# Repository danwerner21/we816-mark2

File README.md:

# WE816-MARK2
The WE816-MARK2 is the second iteration of a 16-bit 65816 based system with 512K of System RAM, 96K of System ROM, a Raspberry PI Pico based graphics processor and an AY-3-8910 Sound chip.  The system runs a custom version of BASIC and supports commodore compatible IEC disk drives.

EhBASIC by Lee Davison was ported to the 65816 CPU on the WE816 computer.   It is designed to allow a full 64K bank for BASIC code and variables with the BASIC interpreter running in a totally different bank. Full documentation on the basic intrepreter can be found in the support folder

---

## Bugs:
* V0.08 board
        U13 should be a 22V10 rather than a 20V8  (no patches required)
        U31 should be 74ALS245 rather than 74AC245 (no patches required)
        The Footprints for the expansion(J7) and Keyboard(J3) connectors are wrong -- special cables are required to connect this version to keyboard and expansion
        RTC IS STILL BROKEN, DO NOT POPULATE U7,U8,X3,C36,C37,C34,R1,R2,R3,U9,BT1,K4,JP1, & JP2

* V0.9 board
        U16 should not be populated -- the wait state generator is not functional, maximum successful tested clock speed is 2.4576 Mhz
        Higher CPU speeds are possible, but the video will not function at much beyond this speed.

## To Do:
* Document Jumper Settings
* Document IO Ports
* Memory Map
* Video speed is not fast enough to deal with a clock speed > (around) 2mhz (2.4576 works perfectly)  Need to add wait state hardware for video
* Add Pictures to this Document
---

## What is included in this repo?
As of this time, the repo includes

1. The WE816-Mark2 Mainboard PCB Kicad design and Gerber files
2. The source code and binaries for the WE816 BASIC interpreter
3. The source code and binaries for the WE816 BIOS firmware
4. The source code and binaries for several hardware test programs
5. The logic equasions for the 4 GALs
6. **OpenSCAD and STL files for a 3d printed case
7. The Firmware for the Raspberry Pi Pico Video  

---

## Known Bugs

### System Jumpers

Jumper P9 -- stereo channel mixer

 *  no jumpers, channel a left, channel c right, channel b left and right
 *  1-2 and 2-3 , channel a,b,c mixed to left and right

Jumper K1 - SRAM chip selection

 * 1&2 - 512K chip used (AS6C4008)
 * 2&3 - 128K chip used (AS6C1008)

Jumper K2 - ROM chip selection

 * 1&2 - 27c256 chip used
 * 2&3 - 29c256 chip used

Jumper K3 - ROM size

 * 1&2 - 16K rom page 0 memory map @ $C000
 * 2&3 - 32K rom page 0 memory map @ $8000

Power P1

 * 1- NC
 * 2-GND
 * 3-GND
 * 4-+5VDC 2A Regulated

Reset P2

 * NO Switch (Short to put system in reset)

Jumper J1, Interrupt Select

* 1&8 UART Interrupt enabled
* 2&7 VIA 1 Interrupt enabled
* 3&6 VIA 2 Interrupt enabled
* 4&5 TMS9918 Interrupt enabled

---

## Video Programming
IO PORTS

Address|Description|Value|Value
--------|--------|----------|--------
$fe30 | Scan Line Emulation | on | off
$fe31 | Display Page | page 0 | page 1
$fe32 | character generator write offset | write offset |
$fe33 | character generator write | Value |
$fe34 | device command  | Command |
$fe35 | Text Mode  | on | off
$fe36 | Lores Mode  | on | off
$fe37 | Double Lores Mode (must be in lores first)  | on | off
$fe38 | Hires Mode | on | off
$fe39 | Double Hires Mode (must be in hires first)  | on | off
$fe3A | 80 Col Mode (must be in text mode)  | on | off
$fe3b | Mixed Mode   (must be in lores/hires first) | on | off
$fe3c | Quad Hires  (must be in hires first) | on | off
$fe3d | Mono Hires  (must be in hires first)| on | off

## Bill Of Materials

### Mainboard

Qty|Reference(s)|Value
--------|--------|----------

### Keyboard
The Keyboard used in the WE816 is identical to the keyboard used in Sergey Kiselev's MSX compatible OMEGA computer.  See the Schematics, PCB layout and build instructions
[here](https://github.com/skiselev/omega/blob/master/Keyboard.md)

### Case
The case in the following images is a 3D print manufactured by the 3D print service offered by JLCPCB.com.  The case was originally designed to be 3D printed by a FDM printer such as the Anycubic Chiron.   It was originally intended that threaded inserts be melted into the stand off posts so the diameter of the holes were sized accordingly.  If a printing service (such as JLCPCB) is used that uses resin printing, it is necessary to slightly drill out the holes in the stand offs so that threaded inserts can be glued in.   It should also be noted that the design tolerances are quite tight and variations in printing can mean that some slight adjusting may be needed in order to get a good fit.

A 12V to 5V converter can be seen in the image that was added into the case in order to convert the 12V power input to the 5B required by the main board.

### Questions?

If there are any questions, I can be reached at vic2020Dan at gmail dot com.

---

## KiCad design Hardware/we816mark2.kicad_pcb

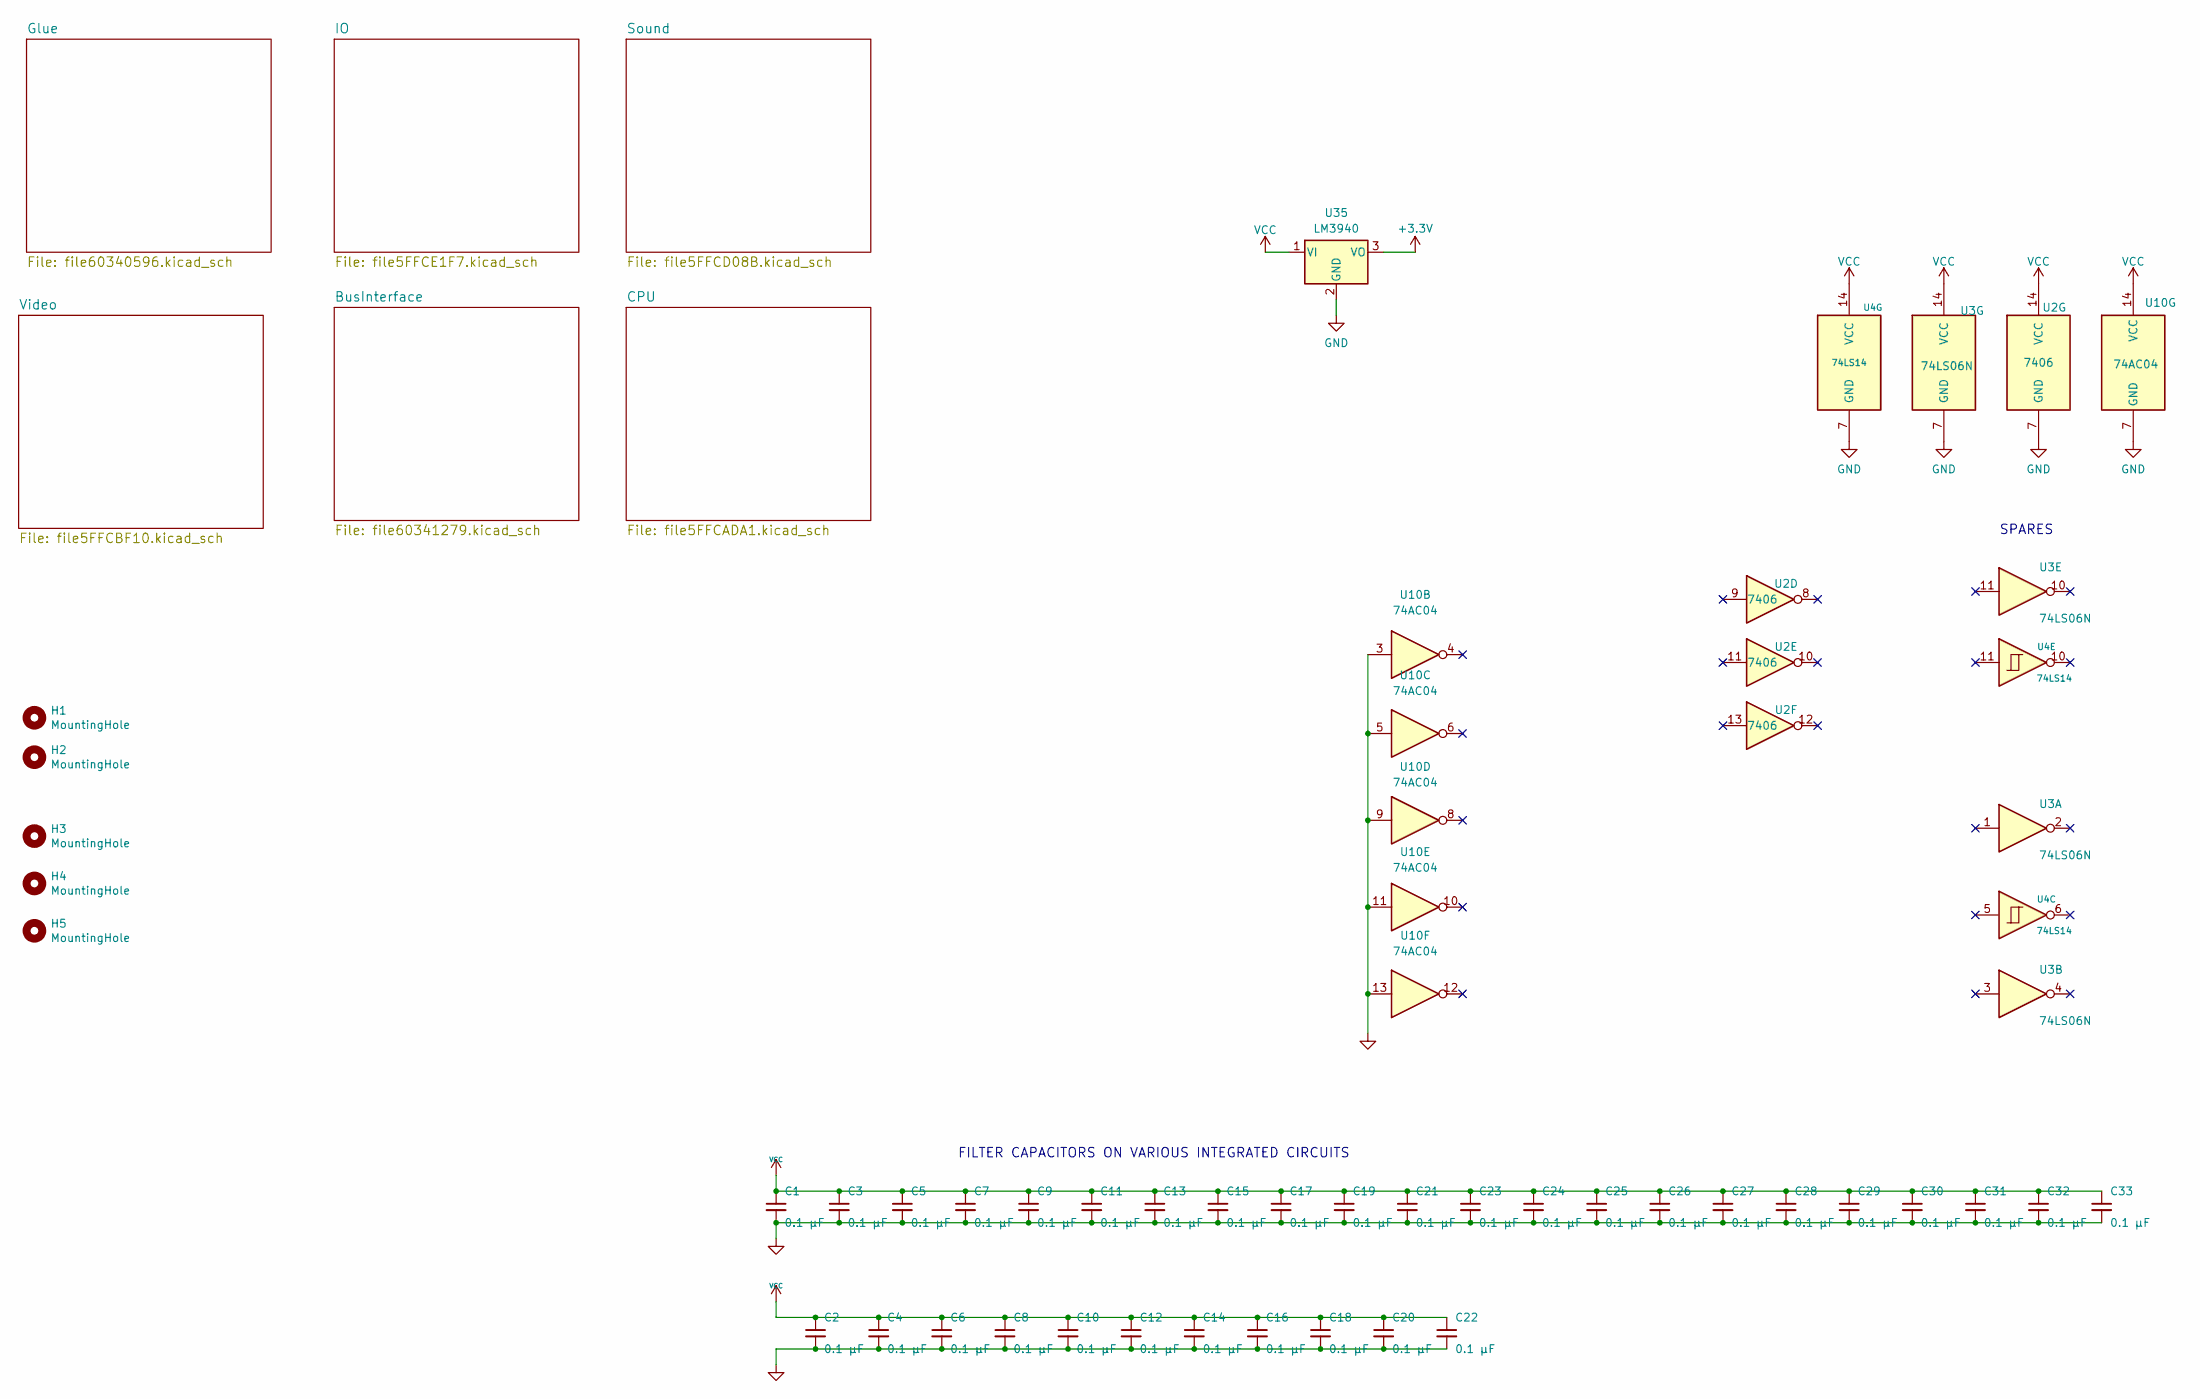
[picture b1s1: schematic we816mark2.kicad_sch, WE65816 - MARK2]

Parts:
C1, C2, C3, C4, C5, C6, C7, C8, C9, C10, C11, C12, C13, C14, C15, C16, C17, C18, C19, C20, C21, C22, C23, C24, C25, C26, C27, C28, C29, C30, C31, C32, C33: 0.1 µF; C_Rect_L7.0mm_W2.0mm_P5.00mm
H1, H2, H3, H4, H5: MountingHole; MountingHole_3.2mm_M3
U2: 7406; DIP-14_W7.62mm_Socket_LongPads
U3: 74LS06N; DIP-14_W7.62mm_Socket_LongPads
U4: 74LS14; DIP-14_W7.62mm_Socket_LongPads
U10: 74AC04; DIP-14_W7.62mm_Socket_LongPads
U35: LM3940; TO-220-3_Vertical

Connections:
+3.3V: U35.3 (VO); also elsewhere on the board
GND: C1.2, C2.2, C3.2, C4.2, C5.2, C6.2, C7.2, C8.2, C9.2, C10.2, C11.2, C12.2, C13.2, C14.2, C15.2, C16.2, C17.2, C18.2, C19.2, C20.2, C21.2, C22.2, C23.2, C24.2, C25.2, C26.2, C27.2, C28.2, C29.2, C30.2, C31.2, C32.2, C33.2, U2.7 (GND), U3.7 (GND), U4.7 (GND), U10.3, U10.5, U10.7 (GND), U10.9, U10.11, U10.13, U35.2 (GND); also elsewhere on the board
VCC: C1.1, C2.1, C3.1, C4.1, C5.1, C6.1, C7.1, C8.1, C9.1, C10.1, C11.1, C12.1, C13.1, C14.1, C15.1, C16.1, C17.1, C18.1, C19.1, C20.1, C21.1, C22.1, C23.1, C24.1, C25.1, C26.1, C27.1, C28.1, C29.1, C30.1, C31.1, C32.1, C33.1, U2.14 (VCC), U3.14 (VCC), U4.14 (VCC), U10.14 (VCC), U35.1 (VI); also elsewhere on the board

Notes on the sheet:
FILTER CAPACITORS ON VARIOUS INTEGRATED CIRCUITS
SPARES

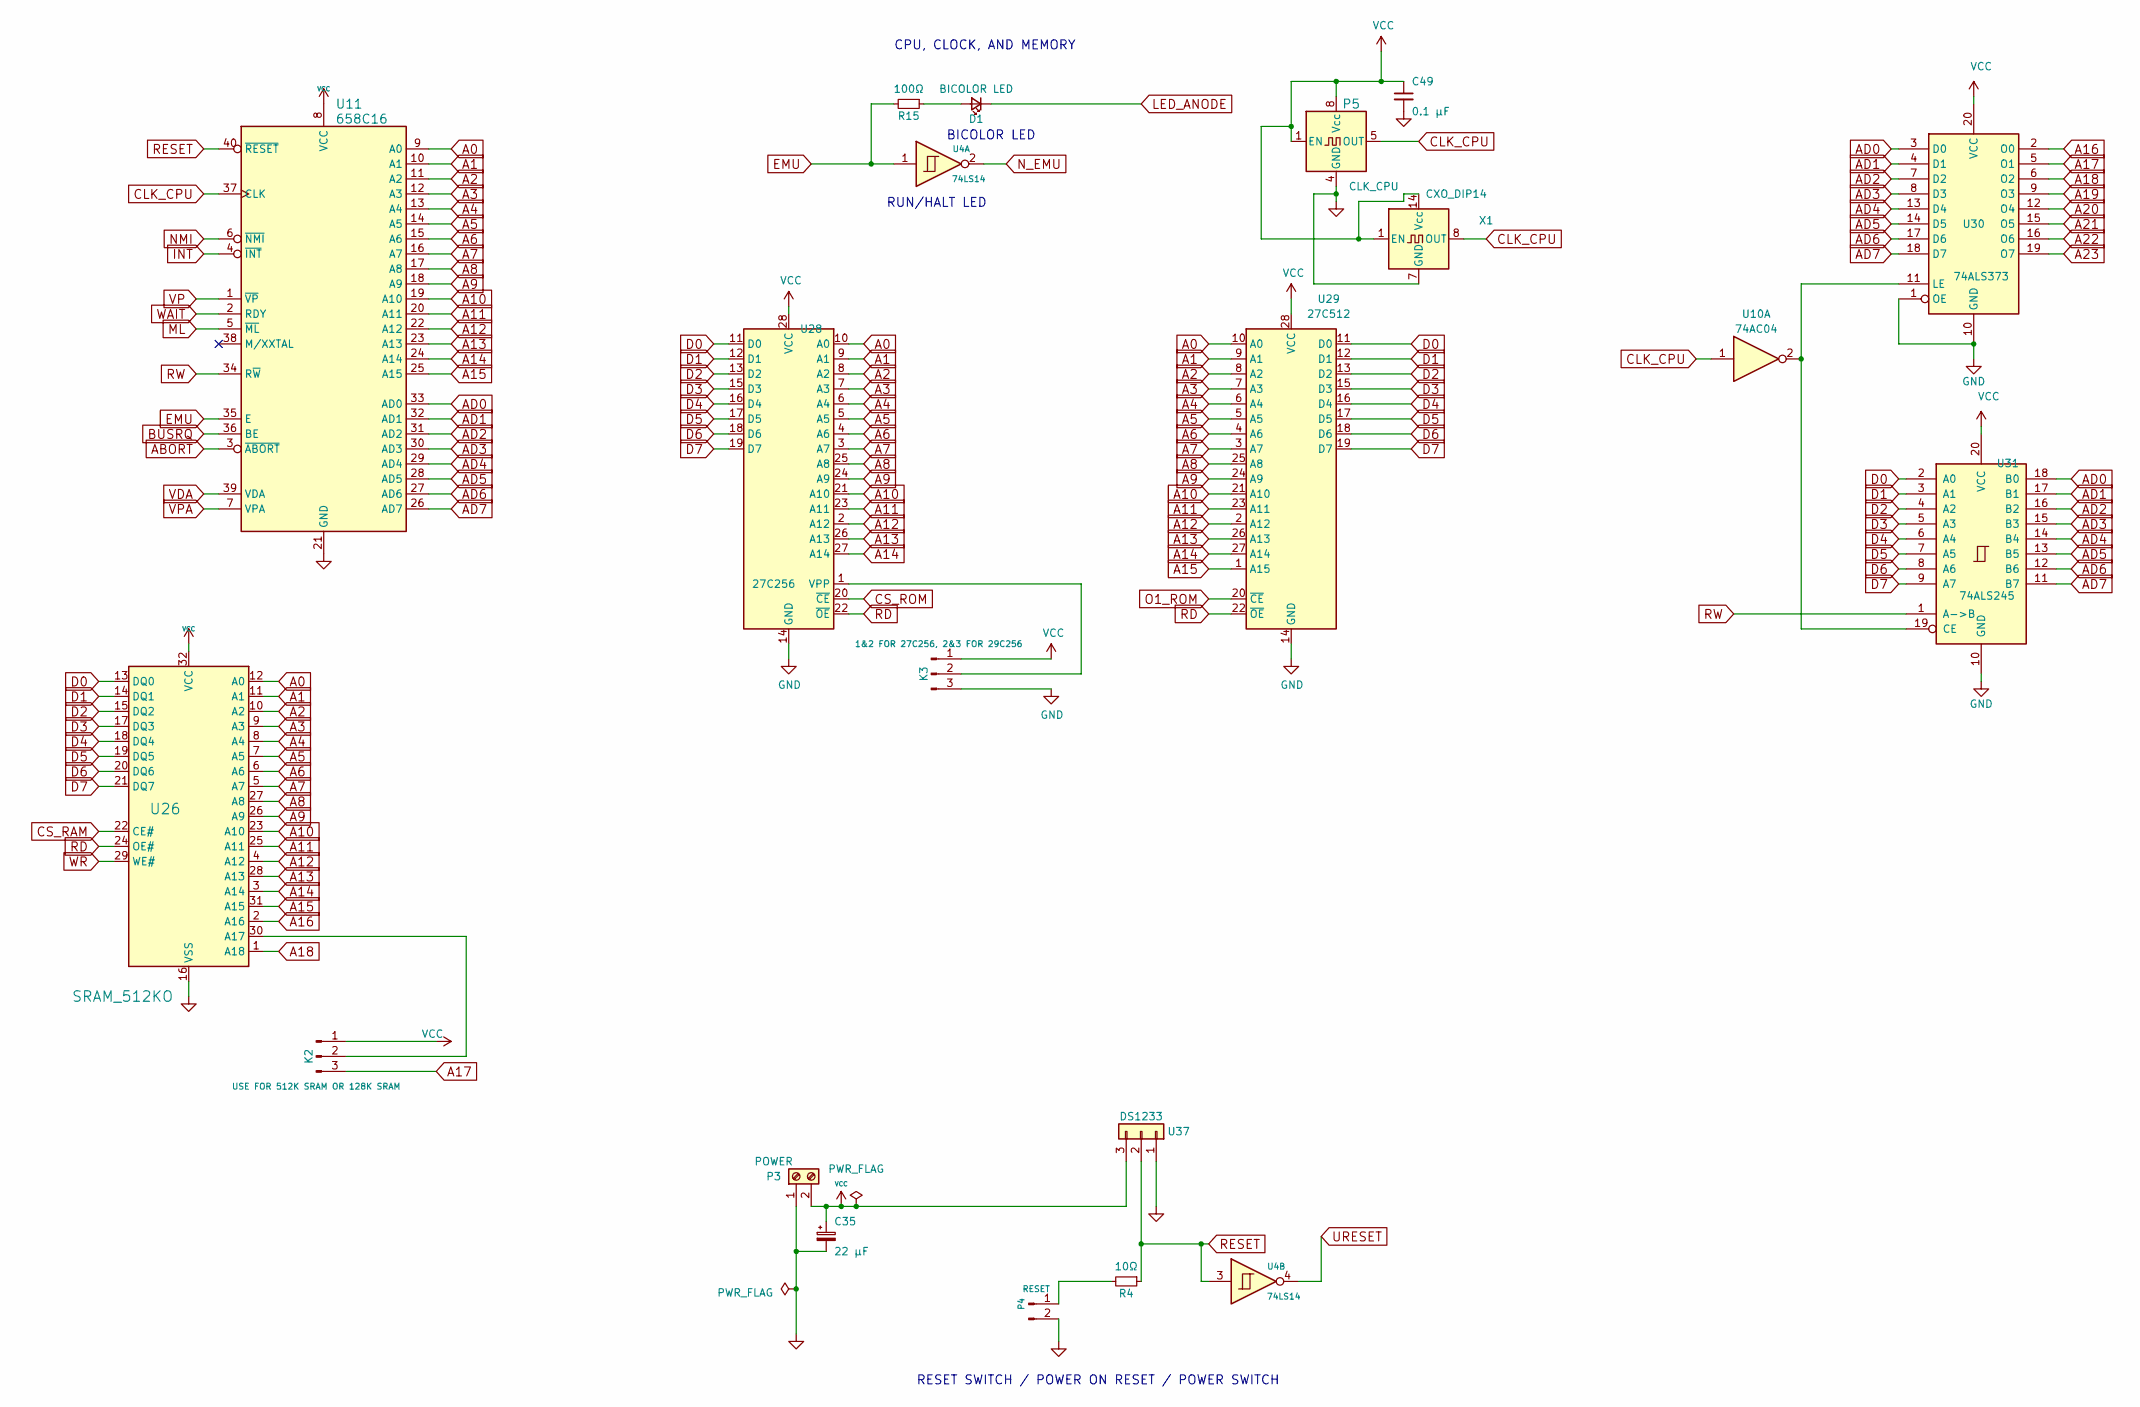
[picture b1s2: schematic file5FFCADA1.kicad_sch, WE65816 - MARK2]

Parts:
C35: 22 µF; CP_Radial_D4.0mm_P2.00mm
C49: 0.1 µF; C_Rect_L7.0mm_W2.0mm_P5.00mm
D1: BICOLOR LED; LED_D5.0mm
K2: USE FOR 512K SRAM OR 128K SRAM; PinHeader_1x03_P2.54mm_Vertical
K3: 1&2 FOR 27C256, 2&3 FOR 29C256; PinHeader_1x03_P2.54mm_Vertical
P3: POWER; TerminalBlock_RND_205-00001_1x02_P5.00mm_Horizontal
P4: RESET; PinHeader_1x02_P2.54mm_Vertical
P5: CLK_CPU; Oscillator_DIP-8
R4: 10Ω; R_Axial_DIN0204_L3.6mm_D1.6mm_P5.08mm_Horizontal
R15: 100Ω; R_Axial_DIN0204_L3.6mm_D1.6mm_P5.08mm_Horizontal
U4: 74LS14; DIP-14_W7.62mm_Socket_LongPads
U10: 74AC04; DIP-14_W7.62mm_Socket_LongPads
U11: 658C16; DIP-40_W15.24mm_Socket_LongPads
U26: SRAM_512KO; DIP-32_W15.24mm_Socket_LongPads
U28: 27C256; DIP-28_W15.24mm_Socket_LongPads
U29: 27C512; DIP-28_W15.24mm_Socket_LongPads
U30: 74ALS373; DIP-20_W7.62mm_Socket_LongPads
U31: 74ALS245; DIP-20_W7.62mm_Socket_LongPads
U37: DS1233; TO-92L_HandSolder
X1: CXO_DIP14; Oscillator_DIP-14

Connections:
A0: U11.9 (A0), U26.12 (A0), U28.10 (A0), U29.10 (A0); also elsewhere on the board
A1: U11.10 (A1), U26.11 (A1), U28.9 (A1), U29.9 (A1); also elsewhere on the board
A2: U11.11 (A2), U26.10 (A2), U28.8 (A2), U29.8 (A2); also elsewhere on the board
A3: U11.12 (A3), U26.9 (A3), U28.7 (A3), U29.7 (A3); also elsewhere on the board
A4: U11.13 (A4), U26.8 (A4), U28.6 (A4), U29.6 (A4); also elsewhere on the board
A5: U11.14 (A5), U26.7 (A5), U28.5 (A5), U29.5 (A5); also elsewhere on the board
A6: U11.15 (A6), U26.6 (A6), U28.4 (A6), U29.4 (A6); also elsewhere on the board
A7: U11.16 (A7), U26.5 (A7), U28.3 (A7), U29.3 (A7); also elsewhere on the board
A8: U11.17 (A8), U26.27 (A8), U28.25 (A8), U29.25 (A8); also elsewhere on the board
A9: U11.18 (A9), U26.26 (A9), U28.24 (A9), U29.24 (A9); also elsewhere on the board
A10: U11.19 (A10), U26.23 (A10), U28.21 (A10), U29.21 (A10); also elsewhere on the board
A11: U11.20 (A11), U26.25 (A11), U28.23 (A11), U29.23 (A11); also elsewhere on the board
A12: U11.22 (A12), U26.4 (A12), U28.2 (A12), U29.2 (A12); also elsewhere on the board
A13: U11.23 (A13), U26.28 (A13), U28.26 (A13), U29.26 (A13); also elsewhere on the board
A14: U11.24 (A14), U26.3 (A14), U28.27 (A14), U29.27 (A14); also elsewhere on the board
A15: U11.25 (A15), U26.31 (A15), U29.1 (A15); also elsewhere on the board
A16: U26.2 (A16), U30.2 (O0); also elsewhere on the board
A17: K2.3, U30.5 (O1); also elsewhere on the board
A18: U26.1 (A18), U30.6 (O2); also elsewhere on the board
A19: U30.9 (O3); also elsewhere on the board
A20: U30.12 (O4); also elsewhere on the board
A21: U30.15 (O5); also elsewhere on the board
A22: U30.16 (O6); also elsewhere on the board
A23: U30.19 (O7); also elsewhere on the board
ABORT: U11.3 (~ABORT); also elsewhere on the board
AD0: U11.33 (AD0), U30.3 (D0), U31.18 (B0)
AD1: U11.32 (AD1), U30.4 (D1), U31.17 (B1)
AD2: U11.31 (AD2), U30.7 (D2), U31.16 (B2)
AD3: U11.30 (AD3), U30.8 (D3), U31.15 (B3)
AD4: U11.29 (AD4), U30.13 (D4), U31.14 (B4)
AD5: U11.28 (AD5), U30.14 (D5), U31.13 (B5)
AD6: U11.27 (AD6), U30.17 (D6), U31.12 (B6)
AD7: U11.26 (AD7), U30.18 (D7), U31.11 (B7)
BUSRQ: U11.36 (BE); also elsewhere on the board
CS_RAM: U26.22 (CE#); also elsewhere on the board
CS_ROM: U28.20 (~CE); also elsewhere on the board
D0: U26.13 (DQ0), U28.11 (D0), U29.11 (D0), U31.2 (A0); also elsewhere on the board
D1: U26.14 (DQ1), U28.12 (D1), U29.12 (D1), U31.3 (A1); also elsewhere on the board
D2: U26.15 (DQ2), U28.13 (D2), U29.13 (D2), U31.4 (A2); also elsewhere on the board
D3: U26.17 (DQ3), U28.15 (D3), U29.15 (D3), U31.5 (A3); also elsewhere on the board
D4: U26.18 (DQ4), U28.16 (D4), U29.16 (D4), U31.6 (A4); also elsewhere on the board
D5: U26.19 (DQ5), U28.17 (D5), U29.17 (D5), U31.7 (A5); also elsewhere on the board
D6: U26.20 (DQ6), U28.18 (D6), U29.18 (D6), U31.8 (A6); also elsewhere on the board
D7: U26.21 (DQ7), U28.19 (D7), U29.19 (D7), U31.9 (A7); also elsewhere on the board
EMU: R15.2, U4.1, U11.35 (E)
GND: C35.2, C49.2, K3.3, P3.1, P4.2, P5.4 (GND), U11.21 (GND), U26.16 (VSS), U28.14 (GND), U29.14 (GND), U30.1 (OE), U30.10 (GND), U31.10 (GND), U37.1, X1.7 (GND); also elsewhere on the board
INT: U11.4 (~INT); also elsewhere on the board
LED_ANODE: D1.1 (K); also elsewhere on the board
ML: U11.5 (~ML); also elsewhere on the board
NMI: U11.6 (~NMI); also elsewhere on the board
N_EMU: U4.2; also elsewhere on the board
unnamed: D1.2 (A), R15.1
unnamed: K2.2, U26.30 (A17)
unnamed: K3.2, U28.1 (VPP)
unnamed: P4.1, R4.2
unnamed: U10.2, U30.11 (LE), U31.19 (CE)
O1_ROM: U29.20 (~CE); also elsewhere on the board
RD: U26.24 (OE#), U28.22 (~OE), U29.22 (~OE); also elsewhere on the board
RESET: R4.1, U4.3, U11.40 (~RESET), U37.2; also elsewhere on the board
RW: U11.34 (R~W), U31.1 (A->B); also elsewhere on the board
URESET: U4.4; also elsewhere on the board
VCC: C35.1, C49.1, K2.1, K3.1, P3.2, P5.1 (EN), P5.8 (Vcc), U11.8 (VCC), U26.32 (VCC), U28.28 (VCC), U29.28 (VCC), U30.20 (VCC), U31.20 (VCC), U37.3, X1.1 (EN), X1.14 (Vcc); also elsewhere on the board
VDA: U11.39 (VDA); also elsewhere on the board
VP: U11.1 (~VP); also elsewhere on the board
VPA: U11.7 (VPA); also elsewhere on the board
WAIT: U11.2 (RDY); also elsewhere on the board
WR: U26.29 (WE#); also elsewhere on the board

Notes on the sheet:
RESET SWITCH / POWER ON RESET / POWER SWITCH
RUN/HALT LED
CPU, CLOCK, AND MEMORY
BICOLOR LED

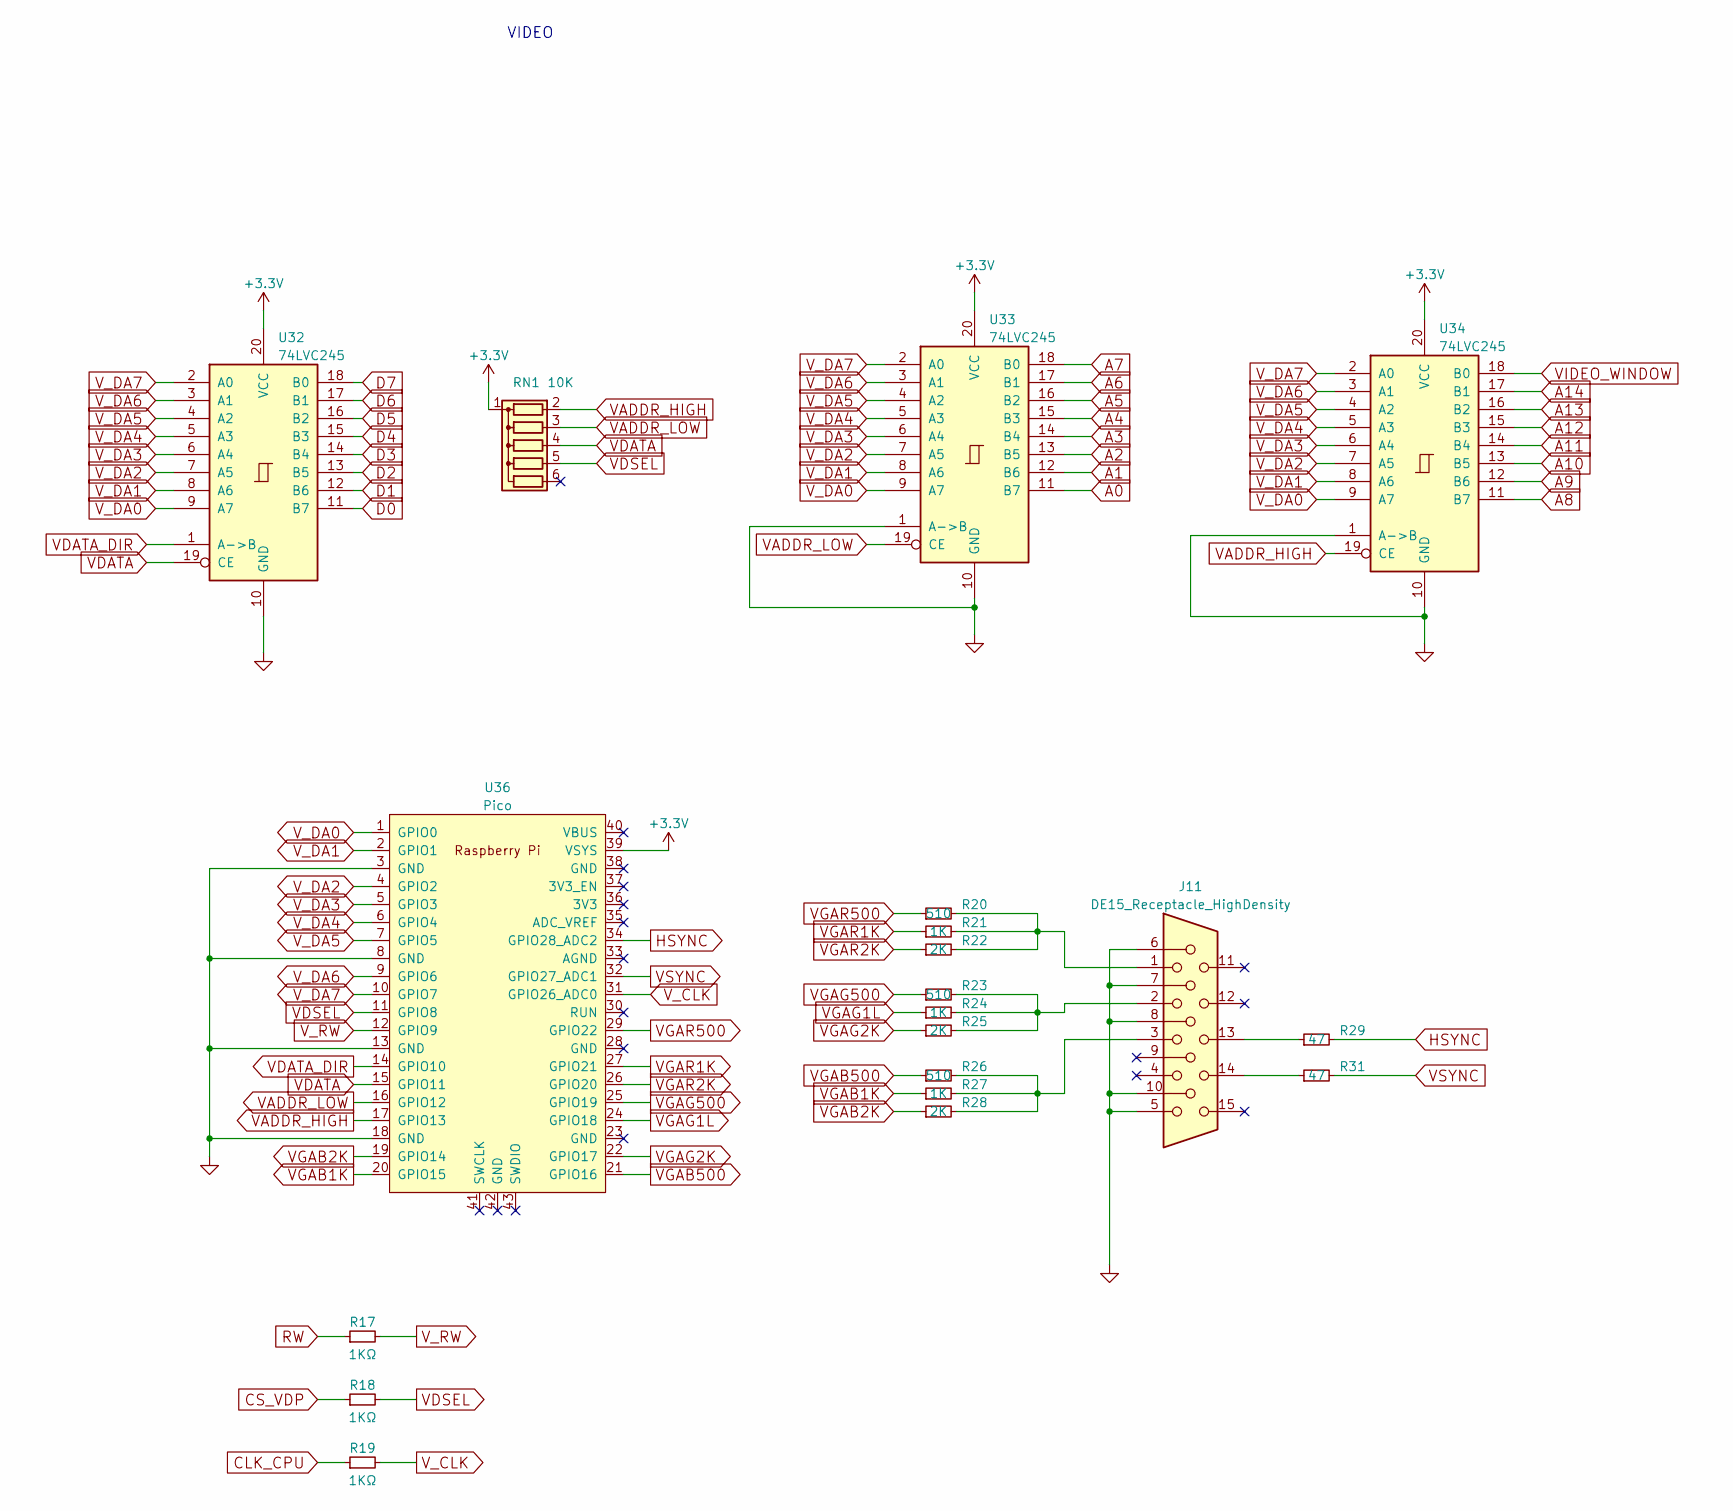
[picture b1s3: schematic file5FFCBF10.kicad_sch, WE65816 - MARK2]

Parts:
J11: DE15_Receptacle_HighDensity; DSUB-15-HD_Female_Horizontal_P2.29x1.98mm_EdgePinOffset3.03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
R17, R18, R19: 1KΩ; R_Axial_DIN0204_L3.6mm_D1.6mm_P5.08mm_Horizontal
R20, R23, R26: 510; R_Axial_DIN0204_L3.6mm_D1.6mm_P5.08mm_Horizontal
R21, R24, R27: 1K; R_Axial_DIN0204_L3.6mm_D1.6mm_P5.08mm_Horizontal
R22, R25, R28: 2K; R_Axial_DIN0204_L3.6mm_D1.6mm_P5.08mm_Horizontal
R29, R31: 47; R_Axial_DIN0204_L3.6mm_D1.6mm_P5.08mm_Horizontal
RN1: 10K; R_Array_SIP6
U32, U33, U34: 74LVC245; DIP-20_W7.62mm_Socket_LongPads
U36: Pico; RPi_Pico_SMD_TH

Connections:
+3.3V: RN1.1 (common), U32.20 (VCC), U33.20 (VCC), U34.20 (VCC), U36.39 (VSYS); also elsewhere on the board
A0: U33.11 (B7); also elsewhere on the board
A1: U33.12 (B6); also elsewhere on the board
A2: U33.13 (B5); also elsewhere on the board
A3: U33.14 (B4); also elsewhere on the board
A4: U33.15 (B3); also elsewhere on the board
A5: U33.16 (B2); also elsewhere on the board
A6: U33.17 (B1); also elsewhere on the board
A7: U33.18 (B0); also elsewhere on the board
A8: U34.11 (B7); also elsewhere on the board
A9: U34.12 (B6); also elsewhere on the board
A10: U34.13 (B5); also elsewhere on the board
A11: U34.14 (B4); also elsewhere on the board
A12: U34.15 (B3); also elsewhere on the board
A13: U34.16 (B2); also elsewhere on the board
A14: U34.17 (B1); also elsewhere on the board
CS_VDP: R18.1; also elsewhere on the board
D0: U32.11 (B7); also elsewhere on the board
D1: U32.12 (B6); also elsewhere on the board
D2: U32.13 (B5); also elsewhere on the board
D3: U32.14 (B4); also elsewhere on the board
D4: U32.15 (B3); also elsewhere on the board
D5: U32.16 (B2); also elsewhere on the board
D6: U32.17 (B1); also elsewhere on the board
D7: U32.18 (B0); also elsewhere on the board
GND: J11.5, J11.6, J11.7, J11.8, J11.10, U32.10 (GND), U33.1 (A->B), U33.10 (GND), U34.1 (A->B), U34.10 (GND), U36.3 (GND), U36.8 (GND), U36.13 (GND), U36.18 (GND); also elsewhere on the board
HSYNC: R29.2, U36.34 (GPIO28_ADC2)
unnamed: J11.1, R20.2, R21.2, R22.2
unnamed: J11.2, R23.2, R24.2, R25.2
unnamed: J11.3, R26.2, R27.2, R28.2
unnamed: J11.13, R29.1
unnamed: J11.14, R31.1
RW: R17.1; also elsewhere on the board
VADDR_HIGH: RN1.2 (R1), U34.19 (CE), U36.17 (GPIO13)
VADDR_LOW: RN1.3 (R2), U33.19 (CE), U36.16 (GPIO12)
VDATA: RN1.4 (R3), U32.19 (CE), U36.15 (GPIO11)
VDATA_DIR: U32.1 (A->B), U36.14 (GPIO10)
VDSEL: R18.2, RN1.5 (R4), U36.11 (GPIO8)
VGAB1K: R27.1, U36.20 (GPIO15)
VGAB2K: R28.1, U36.19 (GPIO14)
VGAB500: R26.1, U36.21 (GPIO16)
VGAG1L: R24.1, U36.24 (GPIO18)
VGAG2K: R25.1, U36.22 (GPIO17)
VGAG500: R23.1, U36.25 (GPIO19)
VGAR1K: R21.1, U36.27 (GPIO21)
VGAR2K: R22.1, U36.26 (GPIO20)
VGAR500: R20.1, U36.29 (GPIO22)
VIDEO_WINDOW: U34.18 (B0); also elsewhere on the board
VSYNC: R31.2, U36.32 (GPIO27_ADC1)
V_CLK: R19.2, U36.31 (GPIO26_ADC0)
V_DA0: U32.9 (A7), U33.9 (A7), U34.9 (A7), U36.1 (GPIO0)
V_DA1: U32.8 (A6), U33.8 (A6), U34.8 (A6), U36.2 (GPIO1)
V_DA2: U32.7 (A5), U33.7 (A5), U34.7 (A5), U36.4 (GPIO2)
V_DA3: U32.6 (A4), U33.6 (A4), U34.6 (A4), U36.5 (GPIO3)
V_DA4: U32.5 (A3), U33.5 (A3), U34.5 (A3), U36.6 (GPIO4)
V_DA5: U32.4 (A2), U33.4 (A2), U34.4 (A2), U36.7 (GPIO5)
V_DA6: U32.3 (A1), U33.3 (A1), U34.3 (A1), U36.9 (GPIO6)
V_DA7: U32.2 (A0), U33.2 (A0), U34.2 (A0), U36.10 (GPIO7)
V_RW: R17.2, U36.12 (GPIO9)

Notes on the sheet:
VIDEO

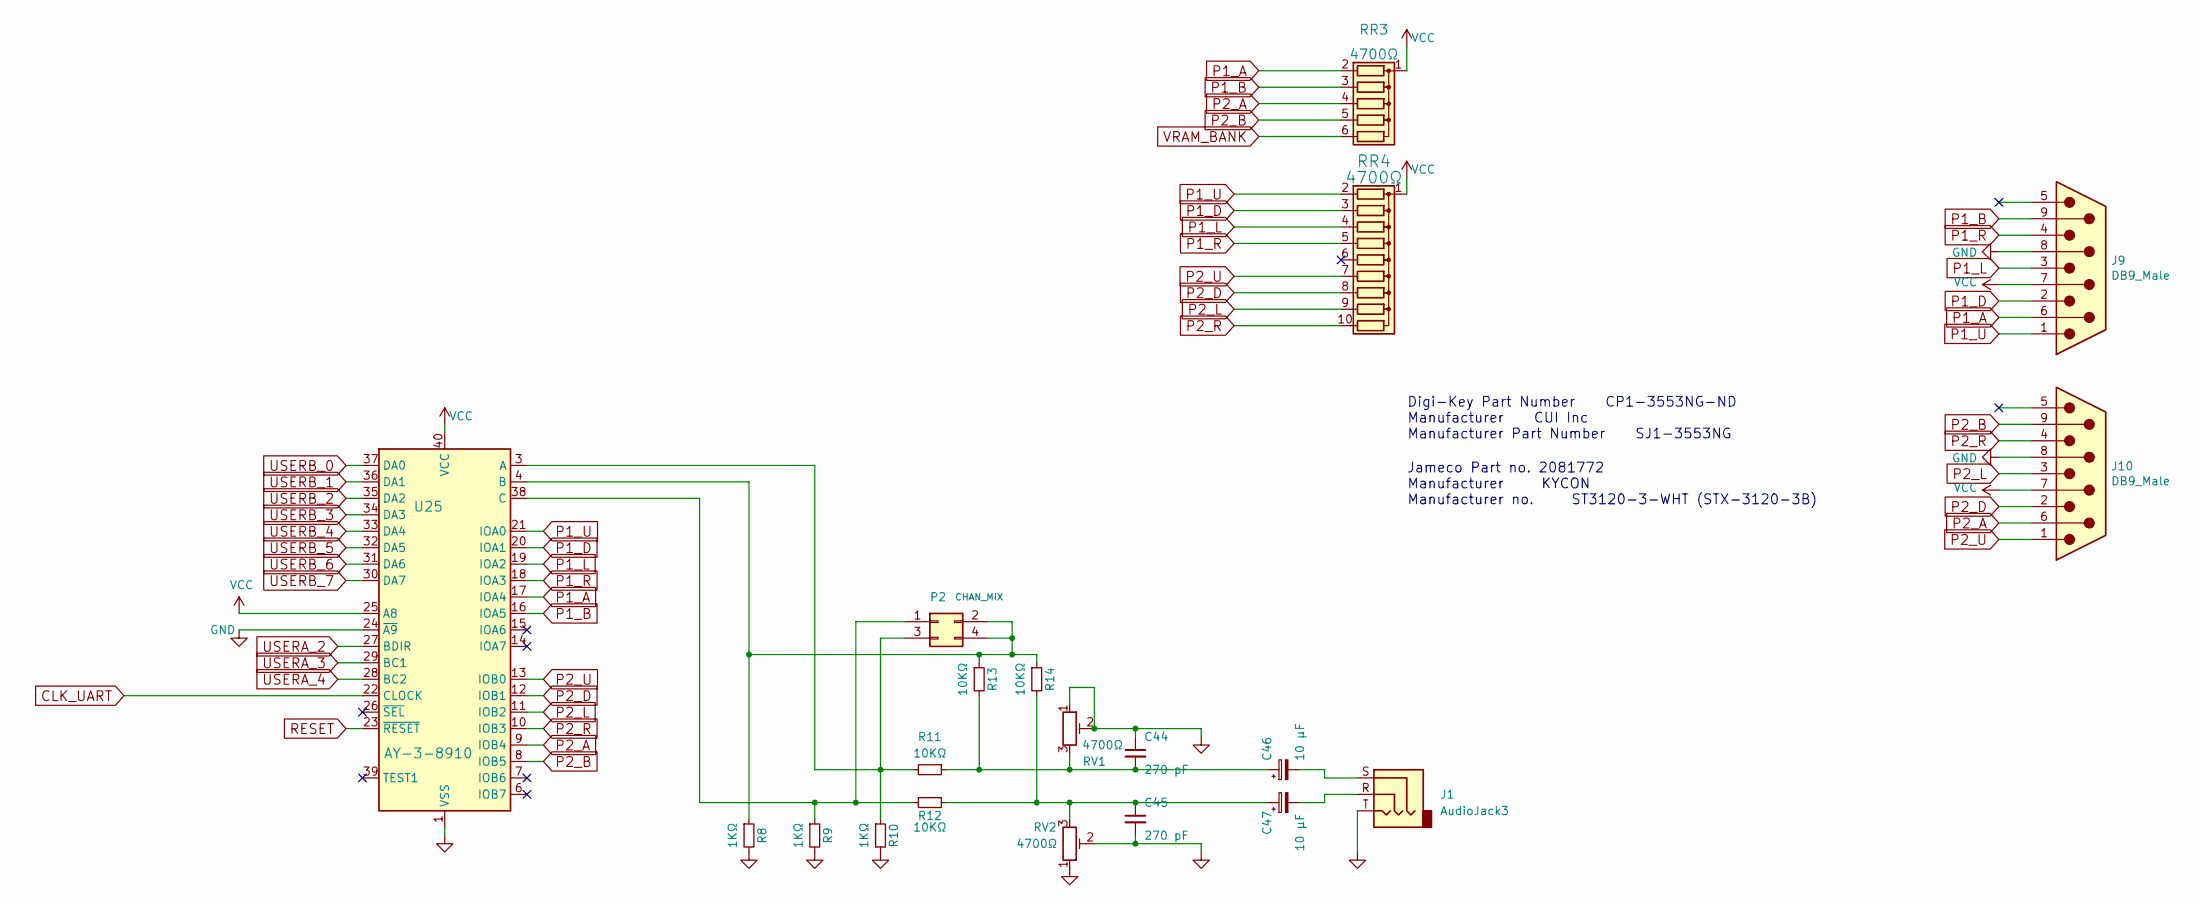
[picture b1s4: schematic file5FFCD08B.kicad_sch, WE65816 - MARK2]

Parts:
C44, C45: 270 pF; C_Rect_L7.0mm_W2.0mm_P5.00mm
C46, C47: 10 µF; CP_Radial_D4.0mm_P2.00mm
J1: AudioJack3; Jack_3.5mm_CUI_SJ1-3533NG_Horizontal_CircularHoles
J9, J10: DB9_Male; DSUB-9_Male_Horizontal_P2.77x2.84mm_EdgePinOffset9.90mm_Hou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
P2: CHAN_MIX; PinHeader_2x02_P2.54mm_Vertical
R8, R9, R10: 1KΩ; R_Axial_DIN0204_L3.6mm_D1.6mm_P5.08mm_Horizontal
R11, R12, R13, R14: 10KΩ; R_Axial_DIN0204_L3.6mm_D1.6mm_P5.08mm_Horizontal
RR3: 4700Ω; R_Array_SIP6
RR4: 4700Ω; R_Array_SIP10
RV1, RV2: 4700Ω; Potentiometer_ACP_CA9-V10_Vertical
U25: AY-3-8910; DIP-40_W15.24mm_Socket_LongPads

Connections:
GND: C44.1, C45.2, J1.T, J9.8, J10.8, R8.2, R9.2, R10.2, RV1.1, RV1.2, RV2.1, RV2.2, U25.1 (VSS), U25.24 (~A9); also elsewhere on the board
unnamed: C44.2, C46.1, R11.1, R13.2, RV1.3
unnamed: C45.1, C47.1, R12.1, R14.2, RV2.3
unnamed: C46.2, J1.S
unnamed: C47.2, J1.R
unnamed: P2.1, R9.1, R12.2, U25.38 (C)
unnamed: P2.2, P2.4, R8.1, R13.1, R14.1, U25.4 (B)
unnamed: P2.3, R10.1, R11.2, U25.3 (A)
P1_A: J9.6, RR3.2 (R1), U25.17 (IOA4)
P1_B: J9.9, RR3.3 (R2), U25.16 (IOA5)
P1_D: J9.2, RR4.3 (R2), U25.20 (IOA1)
P1_L: J9.3, RR4.4 (R3), U25.19 (IOA2)
P1_R: J9.4, RR4.5 (R4), U25.18 (IOA3)
P1_U: J9.1, RR4.2 (R1), U25.21 (IOA0)
P2_A: J10.6, RR3.4 (R3), U25.9 (IOB4)
P2_B: J10.9, RR3.5 (R4), U25.8 (IOB5)
P2_D: J10.2, RR4.8 (R7), U25.12 (IOB1)
P2_L: J10.3, RR4.9 (R8), U25.11 (IOB2)
P2_R: J10.4, RR4.10 (R9), U25.10 (IOB3)
P2_U: J10.1, RR4.7 (R6), U25.13 (IOB0)
RESET: U25.23 (~RESET); also elsewhere on the board
USERA_2: U25.27 (BDIR); also elsewhere on the board
USERA_3: U25.29 (BC1); also elsewhere on the board
USERA_4: U25.28 (BC2); also elsewhere on the board
USERB_0: U25.37 (DA0); also elsewhere on the board
USERB_1: U25.36 (DA1); also elsewhere on the board
USERB_2: U25.35 (DA2); also elsewhere on the board
USERB_3: U25.34 (DA3); also elsewhere on the board
USERB_4: U25.33 (DA4); also elsewhere on the board
USERB_5: U25.32 (DA5); also elsewhere on the board
USERB_6: U25.31 (DA6); also elsewhere on the board
USERB_7: U25.30 (DA7); also elsewhere on the board
VCC: J9.7, J10.7, RR3.1 (common), RR4.1 (common), U25.25 (A8), U25.40 (VCC); also elsewhere on the board
VRAM_BANK: RR3.6 (R5); also elsewhere on the board

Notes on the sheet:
Digi-Key Part Number CP1-3553NG-ND Manufacturer CUI Inc Manufacturer Part Number SJ1-3553NG
Jameco Part no. 2081772 Manufacturer KYCON Manufacturer no. ST3120-3-WHT (STX-3120-3B)
